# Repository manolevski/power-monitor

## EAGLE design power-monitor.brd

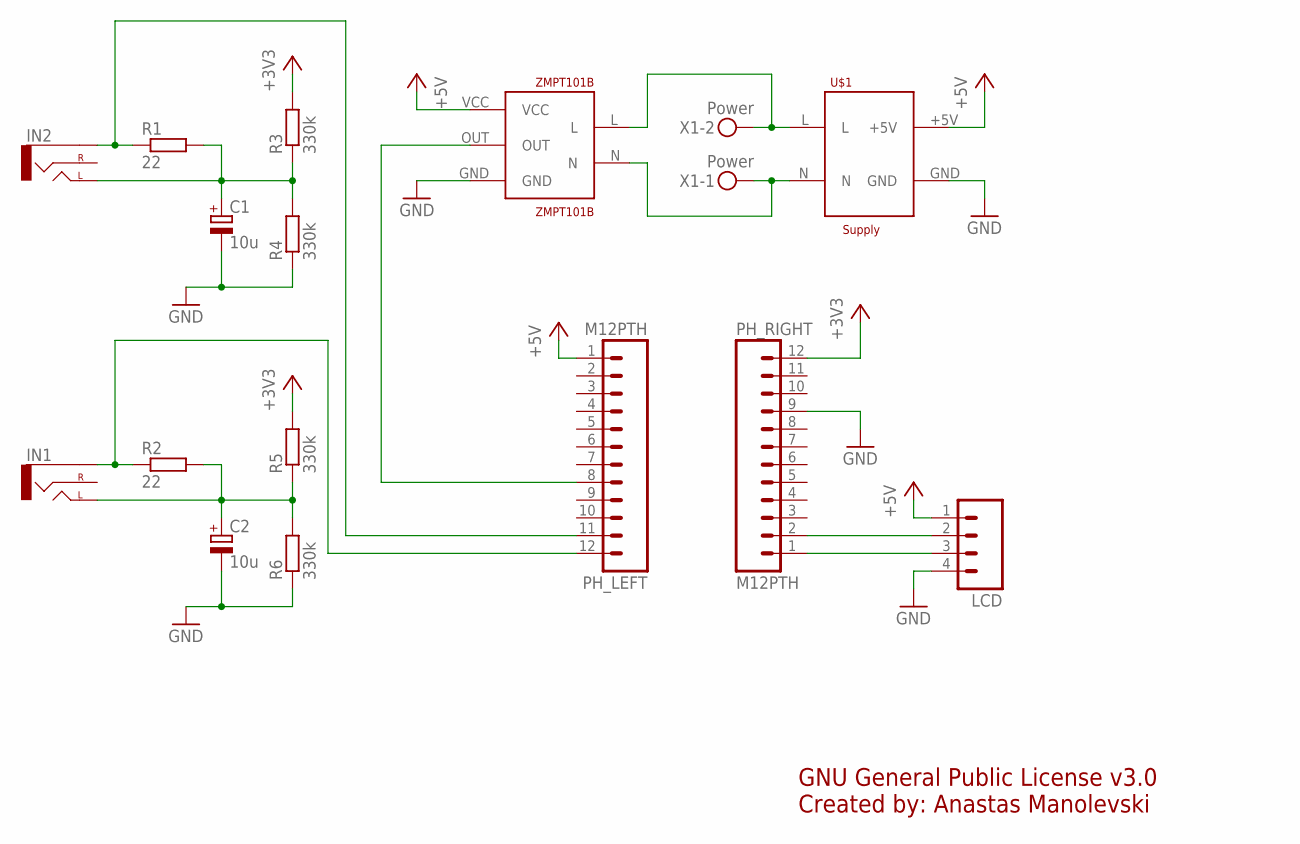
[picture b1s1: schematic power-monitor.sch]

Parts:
C1, C2: 10u; E2,5-5
IN1, IN2: AUDIO-JACKPTH; AUDIO-JACK
LCD: M04PTH; 1X04
PH_LEFT: M12PTH; 1X12-SMALL-PADS
PH_RIGHT: M12PTH; 1X12-SMALL-PADS
R1, R2: 22; 0204/7
R3, R4, R5, R6: 330k; 0204/7
U$1: Supply; PWR-SUPP
X1: Power; MKDSN1,5/2-5,08
ZMPT101B: ZMPT101B

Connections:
+3V3: PH_RIGHT.12, R3.2, R5.2
+5V: LCD.1, PH_LEFT.1, U$1.+5V, ZMPT101B.VCC
GND: C1.-, C2.-, LCD.4, PH_RIGHT.9, R4.1, R6.1, U$1.GND, ZMPT101B.GND
unnamed: IN1.SLEEVE, PH_LEFT.12, R2.1
unnamed: C1.+, IN2.TIP (LEFT), R1.2, R3.1, R4.2
unnamed: IN2.SLEEVE, PH_LEFT.11, R1.1
unnamed: C2.+, IN1.TIP (LEFT), R2.2, R5.1, R6.2
unnamed: LCD.3, PH_RIGHT.1
unnamed: LCD.2, PH_RIGHT.2
unnamed: PH_LEFT.8, ZMPT101B.OUT
unnamed: U$1.L, X1.2, ZMPT101B.L
unnamed: U$1.N, X1.1, ZMPT101B.N

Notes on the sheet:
GNU General Public License v3.0 Created by: Anastas Manolevski

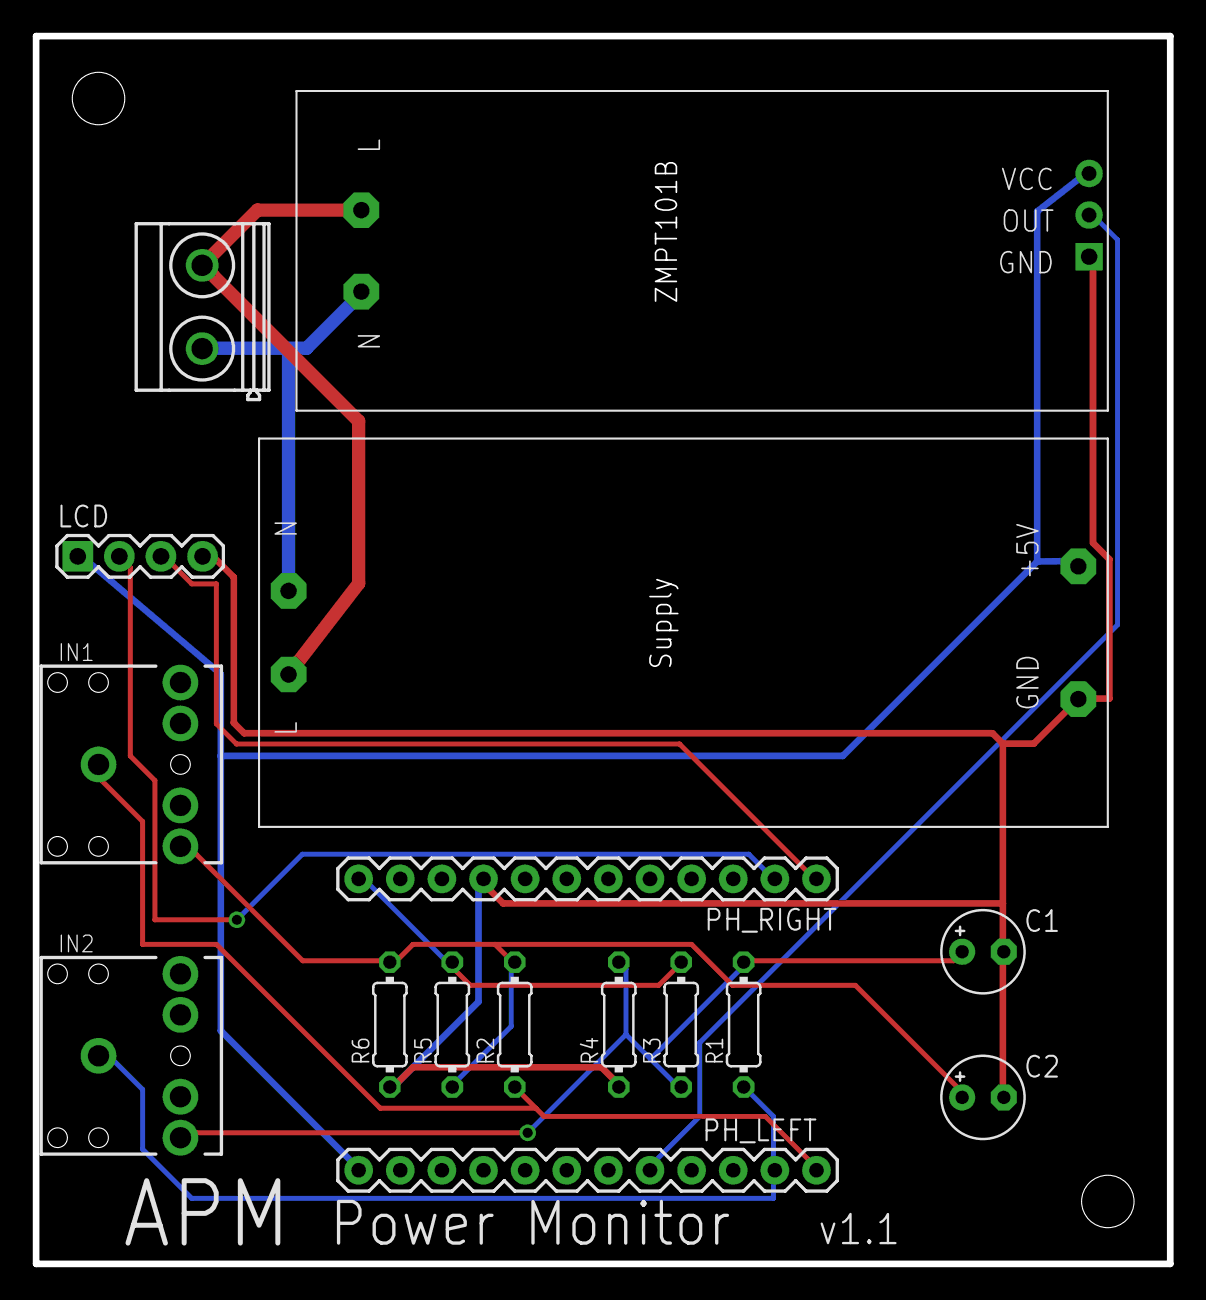
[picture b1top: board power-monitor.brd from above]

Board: 2 copper layers, 69.2 x 74.9 mm, 16 parts (0 on the bottom side), 12 nets.

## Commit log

2017-05-14 Uploading the project

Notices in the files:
parts and their libraries:
SparkFun-Connectors: Licensing: Creative Commons ShareAlike 4.0 International - https://creativecommons.org/licenses/by-sa/4.0
